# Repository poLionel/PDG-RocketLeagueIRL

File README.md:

# PDG-RocketLeagueIRL

A real-world implementation of Rocket League using remote-controlled cars with real-time game management and mobile control interfaces.

**Live Demo:** https://polionel.github.io/PDG-RocketLeagueIRL/

## Project Overview

PDG-RocketLeagueIRL brings the popular video game Rocket League into the physical world. Players control real RC cars on a physical field to play soccer, complete with live scoring, game management, and spectator features.

### Key Features

- **Real-time Car Control**: Control RC cars through mobile app with precision steering and boost capabilities
- **Cross-platform Mobile App**: .NET MAUI application for iOS and Android
- **WebSocket Communication**: Real-time bidirectional communication between app, server, and cars
- **Bluetooth Integration**: Direct car communication via BLE for low-latency control
- **Live Camera Feeds**: Real-time video streaming from car-mounted cameras
- **Game Management**: Complete match management with scoring, timing, and administration
- **Multi-player Support**: Support for multiple cars and players simultaneously
- **Spectator Mode**: Live match viewing with real-time score updates

## Architecture

```
PDG-RocketLeagueIRL/
├── server/          # Python WebSocket server & game management
├── cars/            # Embedded firmware (PlatformIO/Arduino)
├── mobileApp/       # .NET MAUI cross-platform mobile app
├── landingPage/     # Project website and documentation
└── docs/           # Project documentation and specifications
```

### System Components

#### Server (`/server`)
- **Technology**: Python with asyncio, WebSocket, and Bluetooth
- **Purpose**: Central game management, car coordination, and real-time communication
- **Features**:
  - WebSocket server for mobile app communication
  - Bluetooth Low Energy (BLE) car communication
  - Game state management and scoring
  - Auto-provisioning and device discovery
  - Docker containerization support

#### Cars (`/cars`)
- **Technology**: PlatformIO/Arduino (ESP32-based)
- **Purpose**: Physical car control and sensor integration
- **Features**:
  - Motor control and steering
  - Camera integration
  - Bluetooth connectivity
  - Battery management
  - WiFi provisioning

#### Mobile App (`/mobileApp`)
- **Technology**: .NET MAUI (C#)
- **Purpose**: User interface for game control and management
- **Architecture**: Clean layered architecture with MVVM pattern
- **Features**:
  - Car selection and control
  - Game administration
  - Real-time match viewing
  - WiFi configuration
  - Cross-platform compatibility (iOS/Android)

#### Landing Page (`/landingPage`)
- **Technology**: HTML, CSS, JavaScript
- **Purpose**: Project showcase and documentation website
- **Features**: Bootstrap-based responsive design

## Quick Start

### Prerequisites

- **For Server**: Python 3.8+, Docker (optional)
- **For Mobile App**: .NET 6+, Visual Studio or VS Code
- **For Cars**: PlatformIO, ESP32 development board
- **For Development**: Git, modern web browser

### 1. Server Setup

```bash
cd server
pip install -r requirements.txt
python main.py
```

Or using Docker:
```bash
cd server
docker-compose up
```

### 2. Mobile App Setup

```bash
cd mobileApp
dotnet restore
dotnet build
# For Android
dotnet build -f net6.0-android
# For iOS
dotnet build -f net6.0-ios
```

### 3. Car Firmware Setup

```bash
cd cars/firmware
pio run
pio upload
```

## User Personas

Our project serves multiple user types:

- **Rocket League Players**: Experienced gamers seeking physical gameplay
- **New Players**: Newcomers discovering the concept for the first time
- **Referees**: Match administrators managing game flow and rules
- **Spectators**: Audience members following matches live
- **Developers**: Contributors extending and maintaining the project

## Development Workflow

We follow a Git-flow branching strategy:

- **`main`**: Production-ready releases
- **`develop`**: Integration branch for ongoing development
- **`feature/*`**: New feature development
- **`release/*`**: Release preparation and stabilization
- **`hotfix/*`**: Critical production fixes

### Version Control

- **Semantic Versioning**: `vMAJOR.MINOR.PATCH` (e.g., v1.2.3)
- **Automated CI/CD**: Triggered on tagged releases
- **Pull Request Reviews**: Required for all changes

## Communication Protocols

### WebSocket API
- **App ↔ Server**: JSON-based real-time communication
- **Commands**: Car movement, game state, administration
- **Responses**: Game updates, car status, match events

### Bluetooth Low Energy (BLE)
- **Server ↔ Cars**: Low-latency direct control
- **Services**: Motor control, camera, sensors, battery
- **Auto-discovery**: Automatic car detection and pairing

## Technology Stack

| Component | Technologies |
|-----------|-------------|
| **Backend** | Python, asyncio, WebSocket, Bluetooth |
| **Mobile** | .NET MAUI, C#, XAML, MVVM |
| **Embedded** | PlatformIO, Arduino, ESP32, C++ |
| **Frontend** | HTML5, CSS3, JavaScript, Bootstrap |
| **Infrastructure** | Docker, Git, CI/CD |

## Documentation

- **[User Stories & Personas](docs/Personas_users_stories.md)**: Detailed user requirements
- **[Development Workflow](docs/Workflow.md)**: Git strategy and development process
- **[Server Documentation](server/readme.md)**: API specifications and setup
- **[Mobile App Documentation](mobileApp/README.md)**: Architecture and build instructions
- **[Car Design Documentation](cars/docs/)**: Hardware and firmware specifications

## Contributing

We welcome contributions! Please see our development workflow documentation and feel free to:

1. Fork the repository
2. Create a feature branch (`git checkout -b feature/amazing-feature`)
3. Commit your changes (`git commit -m 'Add amazing feature'`)
4. Push to the branch (`git push origin feature/amazing-feature`)
5. Open a Pull Request

## License

This project is part of a academic coursework (PDG - Projet de Groupe).

## Demonstration

Check out our live demonstration and project showcase at: https://polionel.github.io/PDG-RocketLeagueIRL/

---

**Built with love by the PDG-RocketLeagueIRL Team**

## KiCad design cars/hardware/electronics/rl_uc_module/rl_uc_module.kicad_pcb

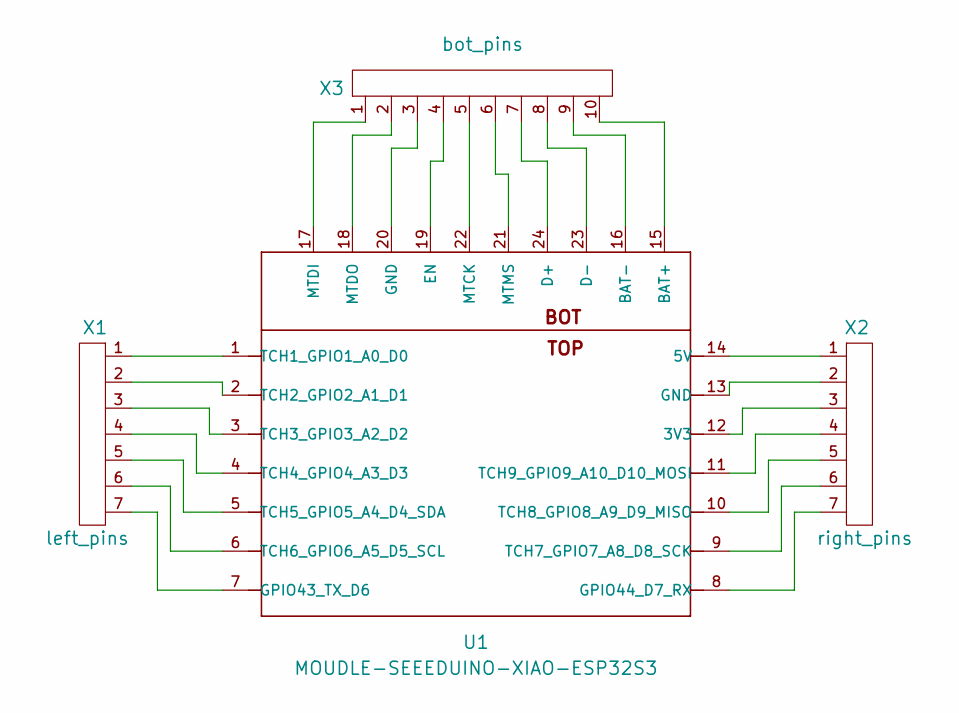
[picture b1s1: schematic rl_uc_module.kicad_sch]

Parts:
U1: MOUDLE-SEEEDUINO-XIAO-ESP32S3; MOUDLE14P-SMD-2.54-21X17.8MM
X1: left_pins; PinHeader_1x07_P2.54mm_Vertical
X2: right_pins; PinHeader_1x07_P2.54mm_Vertical
X3: bot_pins; PinHeader_1x10_P2.54mm_Vertical

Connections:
unnamed: U1.12 (3V3), X2.3
unnamed: U1.14 (5V), X2.1
unnamed: U1.15 (BAT+), X3.10
unnamed: U1.16 (BAT-), X3.9
unnamed: U1.24 (D+), X3.7
unnamed: U1.23 (D-), X3.8
unnamed: U1.19 (EN), X3.4
unnamed: U1.13 (GND), X2.2
unnamed: U1.20 (GND), X3.3
unnamed: U1.7 (GPIO43_TX_D6), X1.7
unnamed: U1.8 (GPIO44_D7_RX), X2.7
unnamed: U1.22 (MTCK), X3.5
unnamed: U1.17 (MTDI), X3.1
unnamed: U1.18 (MTDO), X3.2
unnamed: U1.21 (MTMS), X3.6
unnamed: U1.1 (TCH1_GPIO1_A0_D0), X1.1
unnamed: U1.2 (TCH2_GPIO2_A1_D1), X1.2
unnamed: U1.3 (TCH3_GPIO3_A2_D2), X1.3
unnamed: U1.4 (TCH4_GPIO4_A3_D3), X1.4
unnamed: U1.5 (TCH5_GPIO5_A4_D4_SDA), X1.5
unnamed: U1.6 (TCH6_GPIO6_A5_D5_SCL), X1.6
unnamed: U1.9 (TCH7_GPIO7_A8_D8_SCK), X2.6
unnamed: U1.10 (TCH8_GPIO8_A9_D9_MISO), X2.5
unnamed: U1.11 (TCH9_GPIO9_A10_D10_MOSI), X2.4

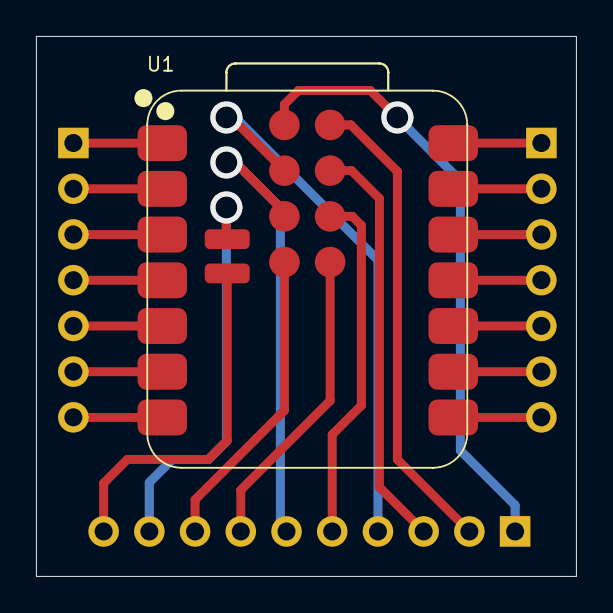
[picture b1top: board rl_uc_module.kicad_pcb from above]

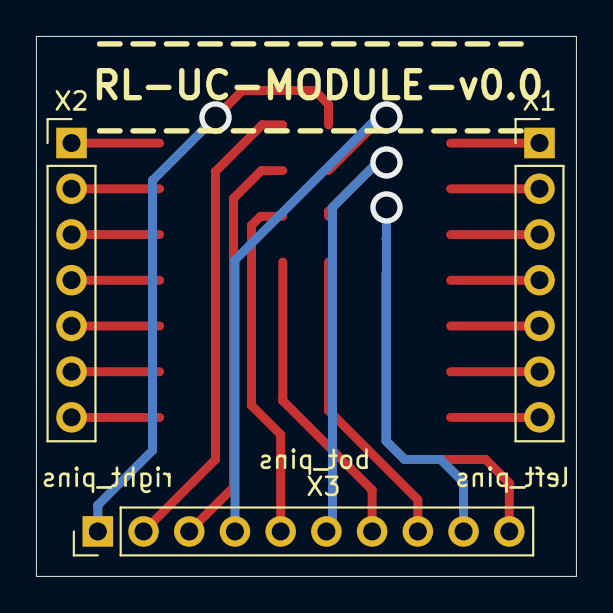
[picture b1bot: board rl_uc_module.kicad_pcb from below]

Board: 2 copper layers, 30.0 x 30.0 mm, 4 parts (3 on the bottom side), 24 nets.

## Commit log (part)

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2025-07-17 initial project skeleton
2025-07-17 ci.yaml correction
2025-07-17 ci.yaml correction v2
2025-07-17 Trigger CI on develop for branch-protection
2025-07-18 folder update
2025-07-18 add landingPage folder
2025-07-22 add release job cd.yaml
2025-07-22 test for merge with rule on develop
2025-07-23 Added first version of landing page
2025-07-23 Fix container layout
2025-07-23 add personas and users stories
2025-07-24 Small changes in the mockup background
2025-07-24 deploy landing page
2025-07-24 fix @v to cancel publish and deploy fail
2025-07-24 update @v to cancel publish and deploy fail
2025-07-25 Demonstration
2025-07-28 bom + design
2025-07-28 structure + add doc open source
2025-07-28 diagram and bom is ok !
2025-07-28 add kicad projet for diagram + bom
2025-07-31 add server functionality with hotspot and CRUD handlers
2025-08-01 Added default maui app
2025-08-01 Renamed solution
2025-08-02 Moved solution to root directory
2025-08-02 Added workload restore to pipeline
2025-08-02 Moved workload restore before dotnet restore
2025-08-02 Modified ci to run on mac os
2025-08-02 Small changes
2025-08-02 Set target to mac os 15
2025-08-02 Set target to mac os 15 large
2025-08-02 Target mac os 15.5
2025-08-02 Added XCode select step
2025-08-02 debug configuration for build
2025-08-07 Added server communication architecture
2025-08-07 Added Bootstrapper and command queue
2025-08-07 Set internals visible to test projects
2025-08-07 Moved service namespace to server namespace
2025-08-07 Added business layer and disabled transitive references in UI layer
2025-08-07 Added comment on game service interface
2025-08-07 Removed line break
2025-08-08 Removed unused sender and listener interfaces
2025-08-08 Added camera feed service
2025-08-08 Added comments
2025-08-08 implement WebSocket server with message handling and CRUD operations; add Docker support and documentation
2025-08-08 Add car management functionality with WebSocket integration
    - Implement Car and CarManager classes for managing car states.
    - Enhance WebSocket server to handle car movement and status requests.
    - Update test WebSocket client to support car selection and status retrieval.
    - Improve error handling and response messaging in WebSocket communication.
2025-08-09 Working on server sender
2025-08-11 add/create all 3D components for chassis design
2025-08-13 Working on PC but needs to test on Raspberry with cars
2025-08-13 Add setup guide for Raspberry Pi Wi-Fi hotspot configuration
2025-08-13 Enhance CI/CD workflows: Add Python setup, dependency installation, linting, and Docker image testing
2025-08-14 Working on listener implementation
2025-08-14 Working on listener processing
2025-08-15 Changed project reference chain
2025-08-18 add firmware project and first compile (env is ready)
2025-08-18 first prototype of BLE worked
2025-08-18 first version of BLE workded
    [MAIN] Boot...
    [MAIN] BLE provisioner initialisé!
    [MAIN] BLE provisioner en attente de connexion...
    [MAIN] Connexion BLE établie
    [MAIN] Identifiants reçus → SSID: 'mon_wifi' | PASS: 'mon_motdepasse'
    [MAIN] Connexion BLE perdue
2025-08-18 first prototype of WiFi worked
    wifi credentials from ble
2025-08-19 Updated documentation following sugestions for app
2025-08-19 Updating app handles to include the changes made to the response JSON
2025-08-19 removed useless test scripts
2025-08-19 change requirements from Bluetooth to bluetooth low energie
2025-08-19 refacto and make moduable ble parte
2025-08-19 Update the bluetooth service to use bluetooth low energery. Needs to be tests but is based on a test code from Rodrigo
2025-08-19 separate defs + fixe ble write + factorise code
2025-08-19 add task connect and monitor all is oke
    [MAIN] [BLE] provisioner init
    [MAIN] [WIFI] provisioner init
    [MAIN] device_id = RL-CAR-d8:3b:da:73:b7:65
    [CONN] attente connexion BLE…
    [MON] actif (surveillance)...
    [MON] perte détectée: BLE=0 WIFI=0
2025-08-21 Working on server listner and sender
2025-08-21 Added test case for protocol
2025-08-21 Working on ci pipeline docker install
2025-08-21 Trying to make docker dependency work
2025-08-21 Trying to avoid building for ios
2025-08-21 Removed orphan project
2025-08-21 add driver motor and battery sensor class
    but not tested
2025-08-21 add cache to optimize docker image build
2025-08-22 add eFuze adc calibration
    Test is ok
2025-08-22 new id maker (chip id) + battery ble reader + task harware
2025-08-23 Working version from html to server to car
2025-08-25 add component feature to soft drive
2025-08-25 add component getteur
2025-08-25 first version of motor drive
    Not tested, i will
2025-08-25 add ble value limits to protect motors
2025-08-25 litle fix and test of limits ok
    [SCAN] Recherche périphérique (Service=7f1f9b2a-6a43-4f62-8c2a-b9d3c0e4a1f0 ou nom 'RL-CAR-*')...
    [SCAN] Trouvé: None @ CC:BA:97:0D:91:09
    [BLE] Connexion à CC:BA:97:0D:91:09 ...
    [BLE] Connecté.
    [DEVID] RL-CAR-08910D97BACC
    [WRITE] SSID='yallo_6317357'
2025-08-25 fix calcul and test ok
    BEFORE--
    Battery : 4.09 / y : -1.00 / x : 0.00 / s : 0.73
    d : Backward / ls : 0.73 / rs : 0.73
    -> Sense ok
    -> max_speed : 4.09*0.73 = 2,98V ok
    -> ls=lr = 0.73 car 2,98v ok !
2025-08-26 add ble class fixes..
2025-08-26 maj of bom
2025-08-26 now also working on the raspberry but needs an bluetooth dongle
2025-08-26 Update to the scan and command phases
2025-08-26 Update comments
2025-08-27 add thread-safe to ble comm
2025-08-27 class camera + init + task vid tested
    [MAIN] [BAT] battery monitor init
    [MAIN] [CAM] camera controller init
    [MAIN] [CAM] -> init successful
    [MAIN] [BLE] provisioner init
2025-08-27 uniforme classes + add secu in to speed calculate
2025-08-27 uniforme battery class name
2025-08-27 edit .ini because drv8833 lib not use
2025-08-27 inits uniforme + tasks management
    not tested
2025-08-27 refacto thread management
    not tested
2025-08-27 Basic structure for views
2025-08-27 Basic implementation for wifiPage and menuPage
2025-08-27 service helper added for binding context
2025-08-27 Working on WIFI implementation
2025-08-27 smal fixe + test ok !
    [MAIN] [MOT] motors controller init
    [MAIN] [MOT] -> init successful
    [MAIN] [BAT] battery monitor init
    [MAIN] [BAT] -> init successful
    [MAIN] [CAM] camera controller init
    [MAIN] [CAM] -> init successful
2025-08-27 Basic game view implementation
2025-08-27 Probably working websocket to ble communication for movement
2025-08-27 Enhance documentation across Bluetooth and WebSocket modules for clarity and maintainability
2025-08-28 new chassis with new motor + add all of step files
2025-08-29 Workingon WIFI selector
2025-08-29 Fixed Wifi selector UI
2025-08-29 Working on wifi selector
2025-08-29 redone models
2025-08-29 Update websocket for new routes for the new game manager
2025-08-29 Update main, readme and test html. Working timing, goals and teams
2025-08-29 Broadcasting some information following some game updates
2025-08-29 Created abstraction layers
2025-08-29 quick fix before merge with other branche
2025-08-29 Added missing mapper
2025-08-29 Added loading
2025-08-29 Improved network UI and added navigation to menu when connected
2025-08-29 Improved UI and bugfix
2025-08-29 placement + route ok
    miss the outline
2025-08-30 Added refresh button and small changes
2025-08-30 Added commands and responses
2025-08-30 Added command processors
2025-08-30 Improved listener and sender exception handling and connection loss
2025-08-30 Working on admin UI
2025-08-30 finish car pcb + restruct the hw repo
2025-08-30 Initial plan
2025-08-30 Create style sheets and refactor XAML to use centralized styles
2025-08-30 Remove remaining hard-coded colors and use centralized color resources
2025-08-30 add interface for carControlService
2025-08-30 add ICarControlService to service collection in boostrapper
2025-08-30 basic structure of game view model
2025-08-30 accelerate and brake command added in viewModel and in view
2025-08-30 Working on UI styles
2025-08-30 Fixed commands and responses
2025-08-30 Working on game updates
2025-08-31 Added missing commands
2025-08-31 Working on data
2025-08-31 UI Improvements
2025-08-31 Added fix for websocket disposal and workarround for data loading
2025-08-31 Added pause time calculation
2025-08-31 Added Car Service
2025-08-31 add game service info
2025-08-31 Added timer service
2025-08-31 Added wifi selector exception handling
2025-08-31 score hud refactored and remove title for each page
2025-08-31 Fixed style on android
2025-08-31 Removed tests the requires car connectivity
2025-08-31 remove progress bar
2025-08-31 Added car selector
2025-08-31 Revert "Added car selector"
    This reverts commit 443416fb8c700fc6b9fb871571de482635844cba.
2025-08-31 timer
2025-08-31 bug - RelayCommand not called when button pressed and released
2025-08-31 Fixed loading mechanism
2025-08-31 add round border for score border
2025-08-31 arthur fait chier pour cela, mais il a raison
2025-08-31 add bracket motor + insert 3d model
2025-09-01 Add comprehensive MAUI app README documentation
2025-09-01 Add relay command for steering value
2025-09-01 fix bug of x:name from game page
2025-09-01 redone the async handlers to broadcast the game stat responds and not the function return
2025-09-01 comments and quick fix for sending command
2025-09-01 Updated dockerfile and compose
2025-09-01 Update wifi to correct ssid and password
2025-09-01 Added the video feed, need the bluetooth part to really test this.
2025-09-01 Added fix for GatewayProvider
2025-09-01 Working on UI fixes
2025-09-01 Removed background color
2025-09-01 Removed flyout menu
2025-09-01 Disabled flyout
2025-09-01 UI and serialization fixes
2025-09-01 Set version
2025-09-01 Fixed tests
2025-09-01 Added undo goal feature
2025-09-01 Revert testing lines
2025-09-02 Working on camera feed encoder and consumption
2025-09-02 Added stream encapsulation and encoder improvements
2025-09-02 add video feed service
2025-09-02 update html tmp
2025-09-02 add wifi info in ble, test ok
    [SCAN] Recherche périphérique (Service=7f1f9b2a-6a43-4f62-8c2a-b9d3c0e4a1f0 ou nom 'RL-CAR-*')...
    [SCAN] Trouvé: None @ CC:BA:97:0D:91:09
    [BLE] Connexion à CC:BA:97:0D:91:09 ...
    [BLE] Connecté.
    [DEVID] RL-CAR-08910D97BACC
    [NET] Lecture infos réseau initiales:
2025-09-02 Fixed decay in boost
2025-09-02 set proper configuration
2025-09-02 Improved null check
2025-09-02 removed useless models.py
2025-09-02 moved the video feed py file
2025-09-02 created auto provisioning service to automaticly send the ssid and password to each car and not have to do it manually
2025-09-02 added new routes to the bluetooth low energy routes for the video stream
2025-09-02 added routes for the video feed but need to clean it a bit up because some routes aren't used anymore
2025-09-02 Remove useless routes which are now in the provisioning service
2025-09-03 add new chassis
2025-09-03 Fixed camera feed view
2025-09-03 change image qualité + core pin + wifi modened
    not tested
2025-09-03 Added camera support
2025-09-03 add boost gesture and effect to view
2025-09-03 edit gesture speed up button in code behind
2025-09-03 UI Improvments
2025-09-03 Async listner improvments
2025-09-03 Added test cars
2025-09-03 Removed test cars
2025-09-03 fully remove test cars
2025-09-03 Added fix for cam in android
2025-09-03 Added camera view on game page
2025-09-03 removed some useless code from websocket
2025-09-03 camera height improvment
2025-09-03 updated ble to remove redundant bluetooth_service
2025-09-03 fixed error for changing car url
2025-09-03 changed url to localhost
2025-09-03 Removed old response
2025-09-03 Added tests
2025-09-03 Fixed protocol tests
2025-09-04 fix CI
2025-09-04 Removed video feed service
2025-09-04 updated the test webpage
2025-09-04 Updated the undo goal to broadcast the news state like the other functions which update the game state
2025-09-04 Updated html for better testing
2025-09-05 Implement multiple client support for car video streams
2025-09-05 readme
2025-09-05 fixe direction from app
2025-09-05 fix car rotation
2025-09-05 add mapper
2025-09-05 map game
